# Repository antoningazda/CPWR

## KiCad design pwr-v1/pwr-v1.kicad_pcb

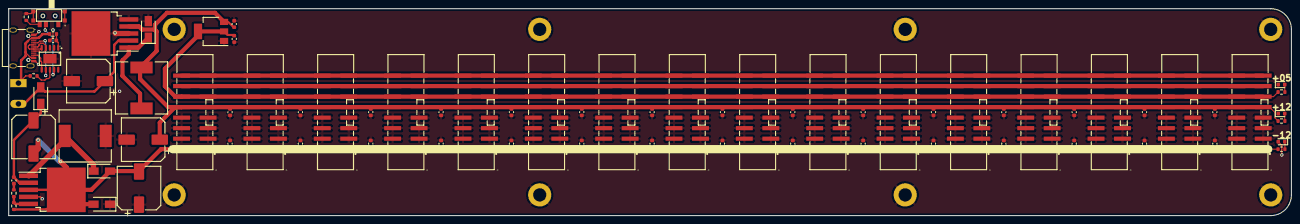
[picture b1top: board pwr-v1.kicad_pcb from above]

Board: 2 copper layers, 310.0 x 50.0 mm, 78 parts (0 on the bottom side), 24 nets.

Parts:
C101: 1u; C_0603_1608Metric
C102, C103, C217, C218, C219, C220, C221, C222, C223, C224, C225, C226, C227, C228, C229, C230: 10u; C_0603_1608Metric
C104: 220u; CP_Elec_10x10
C105, C107, C108: 680u; CP_Elec_10x10
C106, C201, C202, C203, C204, C205, C206, C207, C208, C209, C210, C211, C212, C213, C214, C215, C216: 100n; C_0603_1608Metric
D101, D102, D106, D107: SS54; D_SMA
D103, D104, D105: LED; LED_0603_1608Metric
EURO201, EURO202, EURO203, EURO204, EURO205, EURO206, EURO207, EURO208, EURO209, EURO210, EURO211, EURO212, EURO213, EURO214, EURO215, EURO216: BH-00098; IDC-SMD_BH-00098
L101: 68UH; L_12x12mm_H6mm
L102: 33UH; L_12x12mm_H8mm
R101: 1k; R_0603_1608Metric
R102: 56k; R_0603_1608Metric
R103: 10k; R_0603_1608Metric
R104, R105: 560; R_0603_1608Metric
R106: 220; R_0603_1608Metric
R107, R108: 47k; R_0603_1608Metric
SW101: SW_SPST; TerminalBlock_Altech_AK300-2_P5.00mm
U101: TYPE-C-31-M-12; USB-C_SMD-TYPE-C-31-M-12
U102: SK-3296S-01-L1; SW-SMD_3P-P1.50_L2.7-W6.6
U103: CH224K; SSOP-10_L5.0-W3.9-P1.00-LS6.0-BL-EP
U104: AMS1117-5.0; SOT-223-3_TabPin2
U105, U106: LM2595S-12; TO-263-5_TabPin3

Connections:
+5V: C103.2, EURO201.11, EURO201.12, EURO202.11, EURO202.12, EURO203.11, EURO203.12, EURO204.11, EURO204.12, EURO205.11, EURO205.12, EURO206.11, EURO206.12, EURO207.11, EURO207.12, EURO208.11, EURO208.12, EURO209.11, EURO209.12, EURO210.11, EURO210.12, EURO211.11, EURO211.12, EURO212.11, EURO212.12, EURO213.11, EURO213.12, EURO214.11, EURO214.12, EURO215.11, EURO215.12, EURO216.11, EURO216.12, R106.1, U104.2 (VO)
+12V: C102.2, C105.1, C201.1, C202.1, C203.1, C204.1, C205.1, C206.1, C207.1, C208.1, C217.1, C218.1, C219.1, C220.1, C221.1, C222.1, C223.1, EURO201.9, EURO201.10, EURO202.9, EURO202.10, EURO203.9, EURO203.10, EURO204.9, EURO204.10, EURO205.9, EURO205.10, EURO206.9, EURO206.10, EURO207.9, EURO207.10, EURO208.9, EURO208.10, EURO209.9, EURO209.10, EURO210.9, EURO210.10, EURO211.9, EURO211.10, EURO212.9, EURO212.10, EURO213.9, EURO213.10, EURO214.9, EURO214.10, EURO215.9, EURO215.10, EURO216.9, EURO216.10, L101.2, R104.1, U104.3 (VI), U105.4 (FB)
-12V: C107.2, C108.2, C209.1, C210.1, C211.1, C212.1, C213.1, C214.1, C215.1, C216.1, C224.1, C225.1, C226.1, C227.1, C228.1, C229.1, C230.1, D106.2 (A), D107.2 (A), EURO201.1, EURO201.2, EURO202.1, EURO202.2, EURO203.1, EURO203.2, EURO204.1, EURO204.2, EURO205.1, EURO205.2, EURO206.1, EURO206.2, EURO207.1, EURO207.2, EURO208.1, EURO208.2, EURO209.1, EURO209.2, EURO210.1, EURO210.2, EURO211.1, EURO211.2, EURO212.1, EURO212.2, EURO213.1, EURO213.2, EURO214.1, EURO214.2, EURO215.1, EURO215.2, EURO216.1, EURO216.2, R105.1, R108.2, U106.3 (GND)
/VDD: C101.2, R101.1, U103.1 (VDD)
CC1: U101.A5 (CC1), U103.7 (CC1)
CC2: U101.B5 (CC2), U103.6 (CC2)
CFG1: U102.2, U103.9 (CFG1)
CV: EURO201.13, EURO201.14, EURO202.13, EURO202.14, EURO203.13, EURO203.14, EURO204.13, EURO204.14, EURO205.13, EURO205.14, EURO206.13, EURO206.14, EURO207.13, EURO207.14, EURO208.13, EURO208.14, EURO209.13, EURO209.14, EURO210.13, EURO210.14, EURO211.13, EURO211.14, EURO212.13, EURO212.14, EURO213.13, EURO213.14, EURO214.13, EURO214.14, EURO215.13, EURO215.14, EURO216.13, EURO216.14
DN: U101.A7 (DN1), U101.B7 (DN2), U103.5 (DM)
DP: U101.A6 (DP1), U101.B6 (DP2), U103.4 (DP)
GATE: EURO201.15, EURO201.16, EURO202.15, EURO202.16, EURO203.15, EURO203.16, EURO204.15, EURO204.16, EURO205.15, EURO205.16, EURO206.15, EURO206.16, EURO207.15, EURO207.16, EURO208.15, EURO208.16, EURO209.15, EURO209.16, EURO210.15, EURO210.16, EURO211.15, EURO211.16, EURO212.15, EURO212.16, EURO213.15, EURO213.16, EURO214.15, EURO214.16, EURO215.15, EURO215.16, EURO216.15, EURO216.16
GND: C101.1, C102.1, C103.1, C104.2, C105.2, C108.1, C201.2, C202.2, C203.2, C204.2, C205.2, C206.2, C207.2, C208.2, C209.2, C210.2, C211.2, C212.2, C213.2, C214.2, C215.2, C216.2, C217.2, C218.2, C219.2, C220.2, C221.2, C222.2, C223.2, C224.2, C225.2, C226.2, C227.2, C228.2, C229.2, C230.2, D101.2 (A), D103.1 (K), D104.2 (A), D105.1 (K), D107.1 (K), EURO201.3, EURO201.4, EURO201.5, EURO201.6, EURO201.7, EURO201.8, EURO202.3, EURO202.4, EURO202.5, EURO202.6, EURO202.7, EURO202.8, EURO203.3, EURO203.4, EURO203.5, EURO203.6, EURO203.7, EURO203.8, EURO204.3, EURO204.4, EURO204.5, EURO204.6, EURO204.7, EURO204.8, EURO205.3, EURO205.4, EURO205.5, EURO205.6, EURO205.7, EURO205.8, EURO206.3, EURO206.4, EURO206.5, EURO206.6, EURO206.7, EURO206.8, EURO207.3, EURO207.4, EURO207.5, EURO207.6, EURO207.7, EURO207.8, EURO208.3, EURO208.4, EURO208.5, EURO208.6, EURO208.7, EURO208.8, EURO209.3, EURO209.4, EURO209.5, EURO209.6, EURO209.7, EURO209.8, EURO210.3, EURO210.4, EURO210.5, EURO210.6, EURO210.7, EURO210.8, EURO211.3, EURO211.4, EURO211.5, EURO211.6, EURO211.7, EURO211.8, EURO212.3, EURO212.4, EURO212.5, EURO212.6, EURO212.7, EURO212.8, EURO213.3, EURO213.4, EURO213.5, EURO213.6, EURO213.7, EURO213.8, EURO214.3, EURO214.4, EURO214.5, EURO214.6, EURO214.7, EURO214.8, EURO215.3, EURO215.4, EURO215.5, EURO215.6, EURO215.7, EURO215.8, EURO216.3, EURO216.4, EURO216.5, EURO216.6, EURO216.7, EURO216.8, L102.2, R102.2, U101.A1 (GND), U101.A12 (GND), U101.B1 (GND), U101.B12 (GND), U102.0, U103.11 (GND), U104.1 (GND), U105.3 (GND), U105.5 (ON/~OFF), U106.4 (FB)
unnamed: C106.1, R107.2
unnamed: C106.2, C107.1, D102.1 (K), U106.2 (VIN)
unnamed: D101.1 (K), L101.1, U105.1 (OUT)
unnamed: D103.2 (A), R104.2
unnamed: D104.1 (K), R105.2
unnamed: D105.2 (A), R106.2
unnamed: D106.1 (K), L102.1, U106.1 (OUT)
unnamed: R102.1, U102.3
unnamed: R103.2, U103.8 (VBUS)
unnamed: R107.1, R108.1, U106.5 (ON/~OFF)
VBUS: R101.2, R103.1, SW101.1 (A), U101.A4 (VBUS), U101.A9 (VBUS), U101.B4 (VBUS), U101.B9 (VBUS)
VBUS_SW: C104.1, D102.2 (A), SW101.2 (B), U105.2 (VIN)

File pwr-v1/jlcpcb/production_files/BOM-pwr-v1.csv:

Comment,Designator,Footprint,LCSC
220u,"C104,C105,C107,C108",CP_Elec_10x10,C116211
100n,"C106,C201,C202,C203,C204,C205,C206,C207,C208,C209,C210,C211,C212,C213,C214,C215,C216",C_0603_1608Metric,C14663
1u,C101,C_0603_1608Metric,C15849
TYPE-C-31-M-12,U101,USB-C_SMD-TYPE-C-31-M-12,C165948
1k,R101,R_0603_1608Metric,C21190
SS54,"D101,D102,D106,D107",D_SMA,C22452
LED,"D103,D104,D105",LED_0603_1608Metric,C2286
220,R106,R_0603_1608Metric,C22962
560,"R104,R105",R_0603_1608Metric,C23204
56k,R102,R_0603_1608Metric,C23206
10k,R103,R_0603_1608Metric,C25804
47k,"R107,R108",R_0603_1608Metric,C25819
BH-00098,"EURO201,EURO202,EURO203,EURO204,EURO205,EURO206,EURO207,EURO208,EURO209,EURO210,EURO211,EURO212,EURO213,EURO214,EURO215,EURO216",IDC-SMD_BH-00098,C2685064
SK-3296S-01-L1,U102,SW-SMD_3P-P1.50_L2.7-W6.6,C319020
AMS1117-5.0,U104,SOT-223-3_TabPin2,C6187
LM2595S-12,"U105,U106",TO-263-5_TabPin3,C90691
33UH,L102,L_12x12mm_H8mm,C9400
10u,"C102,C103,C217,C218,C219,C220,C221,C222,C223,C224,C225,C226,C227,C228,C229,C230",C_0603_1608Metric,C96446
CH224K,U103,SSOP-10_L5.0-W3.9-P1.00-LS6.0-BL-EP,C970725
68UH,L101,L_12x12mm_H6mm,C9907

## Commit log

2022-11-19 DUMP
2022-11-20 Fix bad edgecuts
